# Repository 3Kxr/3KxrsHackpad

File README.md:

# 3Kxr’s Hackpad v1.1

> To facilitate the implementation of hotkeys, four keys were designed, whose functions are inspired by the Stream Deck. However, since the Stream Deck is too expensive, I designed this macro keyboard as my own.

Bom：
   -  4x Cherry MX Switches
   -  2x SK6812 MINI-E Leds
   -  1x XIAO RP2040
   -  4x Blank DSA Keycaps
   -  4x M3x16 Bolt
   -  4x M3 Heatset
   -  1x EC11 Rotary encoders

Others:

    KMK Firmware
    3Kxr's HackPad v1.1 top case.stl
    3Kxr's HackPad v1.1 case.stl
    3Kxr HackPad v1.1 assembled.stl

### Schematic

### PCB

### Case

### Assemble

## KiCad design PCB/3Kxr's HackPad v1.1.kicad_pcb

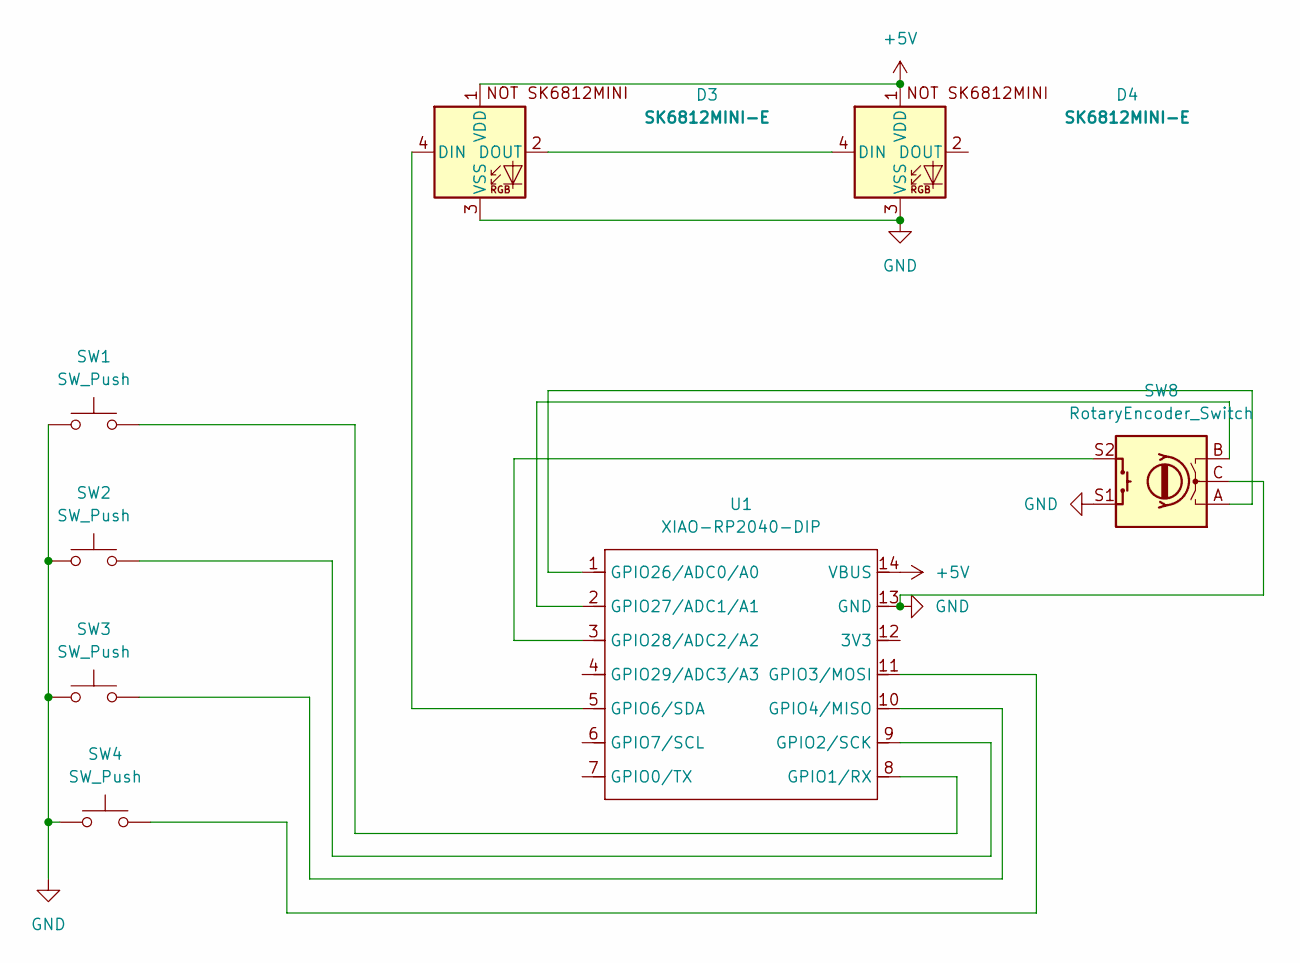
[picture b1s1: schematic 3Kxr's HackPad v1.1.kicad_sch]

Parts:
D3, D4: SK6812MINI-E; SK6812MINI-E_fixed
SW1, SW2, SW3, SW4: SW_Push; SW_Cherry_MX_1.00u_PCB
SW8: RotaryEncoder_Switch; RotaryEncoder_Alps_EC11E-Switch_Vertical_H20mm
U1: XIAO-RP2040-DIP

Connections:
+5V: D3.1 (VDD), D4.1 (VDD), U1.14 (VBUS)
GND: D3.3 (VSS), D4.3 (VSS), SW1.1, SW2.1, SW3.1, SW4.1, SW8.C, SW8.S1, U1.13 (GND)
unnamed: D3.4 (DIN), U1.5 (GPIO6/SDA)
unnamed: D3.2 (DOUT), D4.4 (DIN)
unnamed: SW1.2, U1.8 (GPIO1/RX)
unnamed: SW2.2, U1.9 (GPIO2/SCK)
unnamed: SW4.2, U1.11 (GPIO3/MOSI)
unnamed: SW3.2, U1.10 (GPIO4/MISO)
unnamed: SW8.A, U1.1 (GPIO26/ADC0/A0)
unnamed: SW8.B, U1.2 (GPIO27/ADC1/A1)
unnamed: SW8.S2, U1.3 (GPIO28/ADC2/A2)

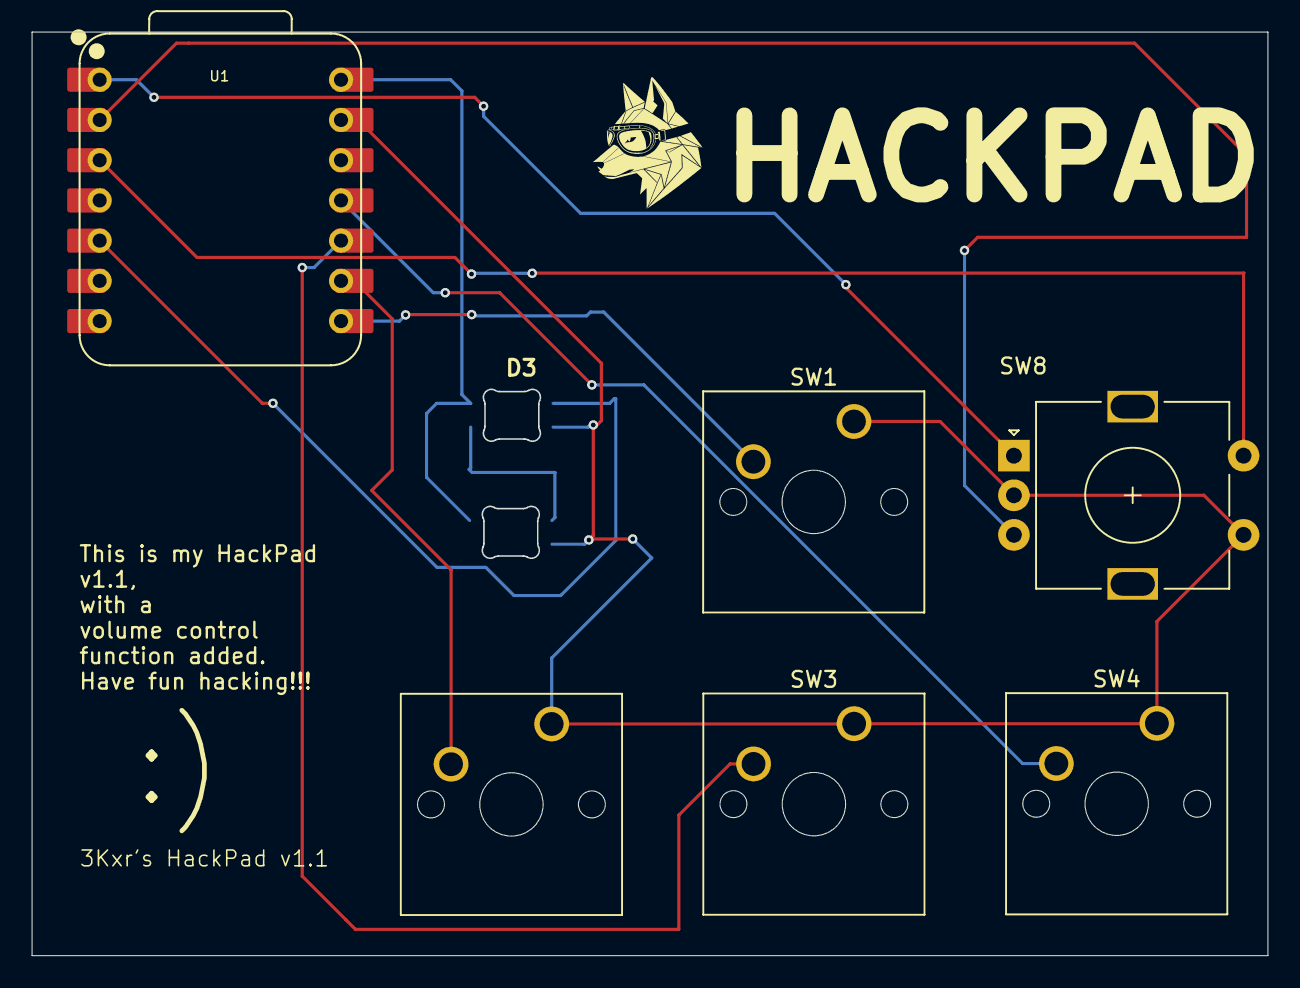
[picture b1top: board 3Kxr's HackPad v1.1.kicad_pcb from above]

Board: 2 copper layers, 78.0 x 58.3 mm, 8 parts (0 on the bottom side), 11 nets.

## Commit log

2026-01-11 add .gitignore
2026-01-11 add files
2026-01-11 add README
2026-01-15 update files
2026-01-16 update top case
2026-01-16 modifed assembed
2026-01-17 update assets
2026-01-17 fix: Modify the top case of EC11 to a square
2026-01-17 refactor: replace SK6812MINI with SK6812MINI-E and reorganize the circuit
2026-01-17 fix: resolve unconnected circuit issue
2026-01-17 reorganize the circuit
2026-01-22 update README description
2026-01-30 Fix routing issues
2026-03-23 add testCode
2026-03-23 fix code
